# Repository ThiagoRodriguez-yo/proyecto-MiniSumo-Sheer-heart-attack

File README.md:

# proyecto-MiniSumo-Sheer-heart-attack
Este proyecto es de el robot Mini Sumo el cual esta diseñado con la finalidad de ser mostrado en una muestra de fin de año donde se muestre las cosas que podría hacer

--Autores--

 * Vazquez Elias
 * Rodriguez Thiago
 * Uriel Ramirez

 --02/10/2025--

 <---------------------------------------->

-Descripcion tecnica: El Mini Sumo es un robot hecho mas que nada para las competencias de robots, tiene una medida de 10x10 (ancho y largo) y un peso limite de 350 gramos en amateur y 500 gramos en competiciones, usualmente el robot mini sumo no tiene un consumo de energia fijo, ya que depende de sus componentes, sin embargo tomando de ejemplo al robot de Arduino que consume unos 46 mA en reposo y 0,03–0,05 kWh por hora con carga, seria considerado como un consumo mensual bajo de 2–4 kWh.

-Objetivos del proyecto: El objetivo de nuestro proyecto es poder enseñar nuestro robot en la muestra de fin de año y que la gente vea como quedo el resultado final de nuestro proyecto

<----------------------------------------->

--Lista de componentes utilizados--

-Sensores-
Modelo: AD32
Detalles técnicos:
– Voltaje de funcionamiento CC: 3.3 V-5 V.
– Corriente de funcionamiento: 20 mAh
– Temperatura de funcionamiento: -10°C a + 50°C
– Distancia de detección: 2 a 40 cm
– Interfaz IO: 4 líneas (- / + / S / EN)
– Señal de salida: nivel TTL
– Dimensiones: 4.5 x 1.1 cm (aprox.)
– Tipo de sensor: Emisor y receptor infrarrojo (IR)
– Número de pines: 4 pines para conexión.
– Ajuste de sensibilidad: Incluye potenciómetro para calibrar la sensibilidad del sensor.

-Sensores de piso-
Características:
- Usando sensores de reflexión infrarroja TCRT5000
- Distancia de reflexión de prueba: 1mm a 25mm
- Limpio y 3, la salida del comparador, Onda de senal,
- La capacidad de conducción es fuerte, por mas de 15 ma.
- Con muchos potenciómetros de precisión ajustables para ajustar la sensibilidad
- Voltaje de funcionamiento de 3,3 V a 5V
- Forma de salida: salida de interruptor digital (0 y 1)
- Tiene un agujero de perno fijo, instalación conveniente
- Tablero pequeño tamaño de PCB: 3,2 cm x 1,4 cm
- LM393, uso de comparador de amplio voltaje
- Tamaño: 3,1×1,3 cm (aprox.)

-Motores-
Modelo: N30 500RPM
Detalles tecnicos:
- Diámetro de 15 mm y longitud total de 47 mm. 
- Corriente: 120 mA en funcionamiento, 3,2 A en parada.
- Par: 3,9 kg-cm , 1,2 kg-cm .
- Peso: 21 gramos.

-Switch-
Llave Palanca Switch Spdt On-on 6a 125v Mts-102 3pin
Modelo: MTS-102
Detalles tecnicos:
- Tipo: DPDT
- Número de pines: 3 pines
- Posición: 2 Posiciones (ON / ON)
- Tamaño: aprox. 31 * 13 * 12 mm
- Voltaje y corriente nominales: CA 125V, 6A

-Circuito del Motor-
Modelo: DIP8
-Tipo de circuito: Integrado
-Tipo TA6586

-Placa-
Modelo: Nodemcu ESP-325 USB-C 38 pines
Detalles tecnicos:
- Voltaje de Alimentación: 5V (USB-C)
- Voltaje de Entrada / Salida: 3.3V
- Puerto USB: USB-C
- SoC: ESP32
- CPU principal: Tensilica Xtensa 32-bit LX6
- Frecuencia de Reloj: hasta 240Mhz
- Desempeño: Hasta 600 DMIPS
- WiFi: 802.11 b/g/n/e/i
- Bluetooth:v4.2 BR/EDR y Bluetooth Low Energy (BLE)
- Pines Digitales GPIO: 24 
- Convesor Analogolico Digital
- UART: 2
- Chip USB-Serial: CP2102
- Antena en PCB
- 38 PINES
- DIMENSIONES: 51 x 25 mm (Largo y Ancho)

  -Seguridad-
- Estándares IEEE 802.11: WFA, WPA/WPA2 y WAPI
- 1,024-bit OTP
- Aceleración Criptográfica por Hardware: AES, HASH (SHA-2), RSA, ECC, RNG

  -Driver de motores-
Características:
- Baja corriente en espera: ≦2 µA
- Amplio rango de tensión de alimentación
- Función de freno integrada
- Protección contra apagado térmico
- Límite de sobrecorriente y protección contra cortocircuitos
- Encapsulado DIP8 sin plomo.

  -Resistencias-
- Cantidad: 6
- Valores: 3 resistencias de 1k y 3 resistencias de 2.2k

  -Capacitores-
- Tipo de capacitores: Electrolitico y Ceramico
- Cantidad: 2 capacitores Electroliticos y 4 capacitores de Marmol
- Valores Electroliticos: 470uf
- Valores Ceramico: 2 de 0.1uf y 2 de 10nf

  -Diseño del circuito-

ESQ:

PCB:

  -Descripcion del funcionamiento-
- Detección de límites: El robot incorpora un sensor infrarrojo ubicado en la parte inferior del chasis, cuya función principal es identificar el borde de la superficie de combate (arena). Ante la detección de un cambio en el color o textura del suelo que indique el límite, el sistema activa una rutina de evasión para evitar que el robot lo cruce.

- Localización del oponente: El robot está equipado con sensores de proximidad, infrarrojos frontales, que permiten detectar la presencia de un contrincante en su campo de acción. Una vez identificado un objetivo, el robot inicia una secuencia de ataque orientada a la intercepción directa.

- Comportamiento ofensivo: El algoritmo de combate prioriza la ofensiva continua. El robot mantiene su trayectoria de ataque hasta que logra desplazar al oponente fuera de los límites del área de combate, momento en el cual se reinicia el ciclo de búsqueda de nuevos objetivos.

  -Montaje-
lijar la placa de cobre
luego conseguir el sticker del pcb 
acto siguiente planchar el sticker en la placa hasta ver que el tóner haya quedado perfectamente adherido a la placa
luego bañar la placa en percloruro por varios minutos
luego sacar la placa del percloruro después de revisar que no haya excedente de cobre
lijar nuevamente para sacar el tóner excedente
agujerear la placa luego de revisar que el cobre innecesario haya sido comido correctamente por el percloruro
iniciar montaje de componentes electrónicos
luego soldar cada componente a la placa (se recomienda usar el material de soldadura Flux) usar estaño para soldar (usar estaño 60% estaño 40% plomo)
luego verificar que no haya cortos
montaje terminado

  -herramientas-
un soldador de punta fina (de 60W)
estaño (60% estaño 40% plomo)
pinzas(de punta y alicate)
flux
chupa estaño y o cinta desoldante

- precauciones: al manejar herramientas peligrosas en manos inexpertas recomendamos el uso de guantes de seguridad y delantal, aunque estos no son obligatorios

-tipo de soldadura: 
Soldadura con aleación de estaño-plomo  

-Datasheet-

AD32: [E3S-A.PDF](https://github.com/user-attachments/files/23096925/E3S-A.PDF)

ESP32: [ESP32.PDF](https://github.com/user-attachments/files/23096990/ESP32.PDF)

TCRT5000:[TCRT5000.PDF](https://github.com/user-attachments/files/23097029/TCRT5000.PDF)

TA6586:[TA6586.PDF](https://github.com/user-attachments/files/23097099/TA6586.PDF)

-Tareas de cada integrante-
- Rodriguez Thiago: PCB, Esquematico
- Elias Vazquez: Carroceria (3D)
- Uriel Ramirez: Montaje de la placa y programacion

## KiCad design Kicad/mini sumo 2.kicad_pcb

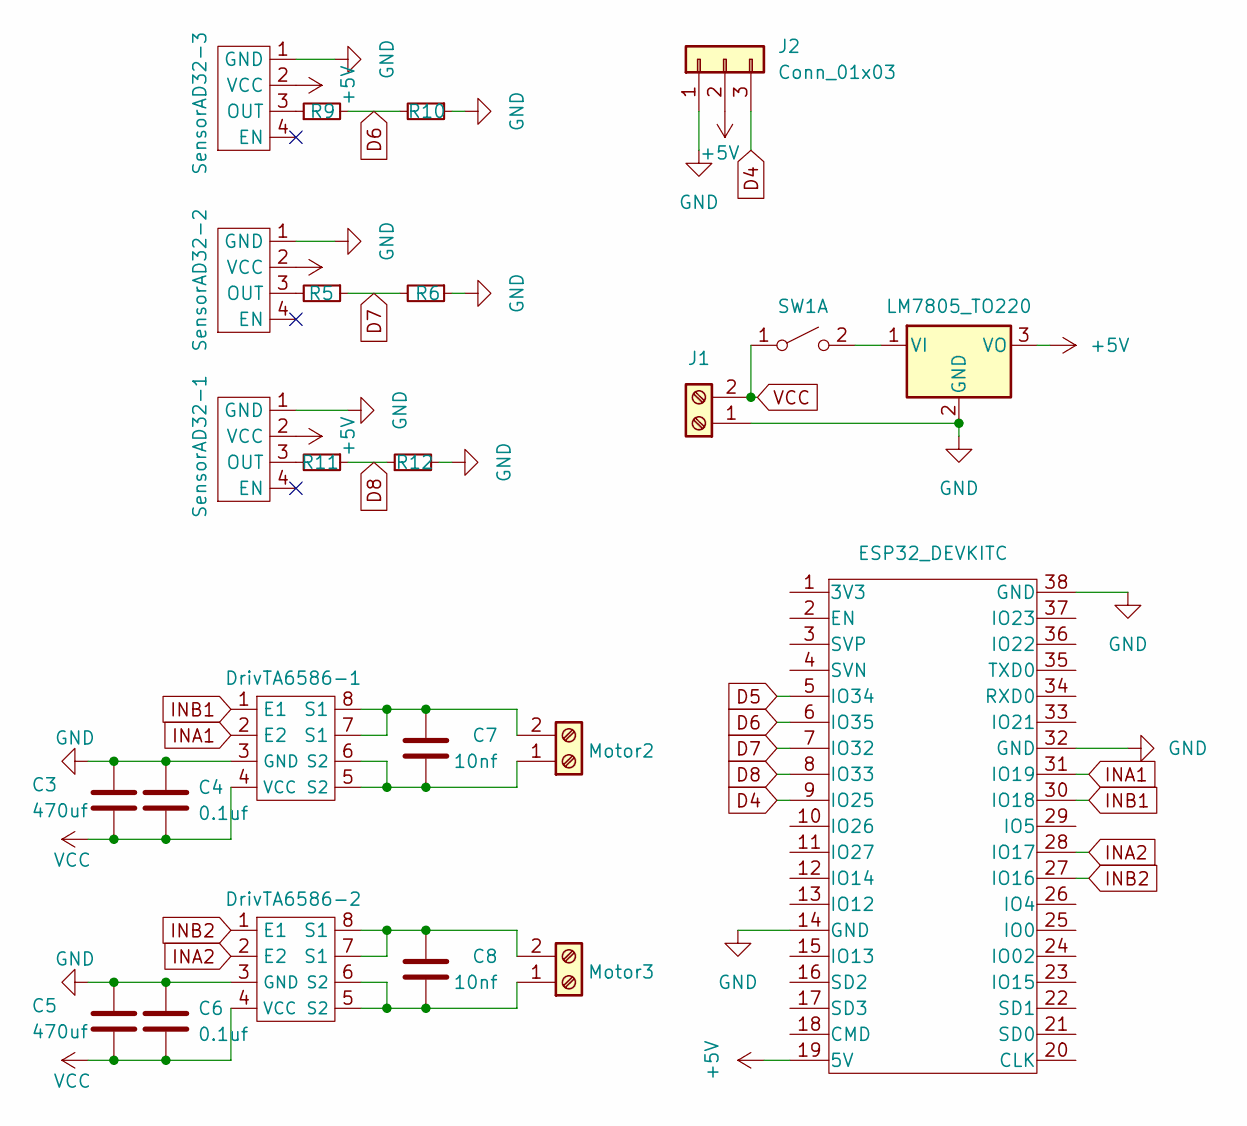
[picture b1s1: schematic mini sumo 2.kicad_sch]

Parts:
C3, C5: 470uf; CP_Radial_D8.0mm_P3.80mm
C4, C6: 0.1uf; C_Disc_D5.0mm_W2.5mm_P2.50mm
C7, C8: 10nf; C_Disc_D5.0mm_W2.5mm_P2.50mm
DrivTA6586-1, DrivTA6586-2: DIP-8_W7.62mm
J1: Screw_Terminal_01x02; TerminalBlock_MaiXu_MX126-5.0-02P_1x02_P5.00mm
J2: Conn_01x03; PinHeader_1x03_P2.54mm_Vertical
Motor2, Motor3: Screw_Terminal_01x02; TerminalBlock_Phoenix_MKDS-1,5-2-5.08_1x02_P5.08mm_Horizont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
R5, R9, R11: 1K; R_Axial_DIN0207_L6.3mm_D2.5mm_P7.62mm_Horizontal
R6, R10, R12: 2.2K; R_Axial_DIN0207_L6.3mm_D2.5mm_P7.62mm_Horizontal
SW1: SW_DPST_x2; SW_SPDT_TH_Vertical
SensorAD32-1, SensorAD32-2, SensorAD32-3: JST-4V
U1: LM7805_TO220; TO-220-3_Vertical
U9: ESP32_DEVKITC; ESP32S

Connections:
+5V: J2.2, SensorAD32-1.2 (VCC), SensorAD32-2.2 (VCC), SensorAD32-3.2 (VCC), U1.3 (VO), U9.19 (5V)
D4: J2.3, U9.9 (IO25)
D5: U9.5 (IO34)
D6: R9.2, R10.2, U9.6 (IO35)
D7: R5.1, R6.2, U9.7 (IO32)
D8: R11.1, R12.1, U9.8 (IO33)
GND: C3.1, C4.1, C5.1, C6.1, DrivTA6586-1.3 (GND), DrivTA6586-2.3 (GND), J1.1, J2.1, R6.1, R10.1, R12.2, SensorAD32-1.1 (GND), SensorAD32-2.1 (GND), SensorAD32-3.1 (GND), U1.2 (GND), U9.14 (GND), U9.32 (GND), U9.38 (GND)
INA1: DrivTA6586-1.2 (E2), U9.31 (IO19)
INA2: DrivTA6586-2.2 (E2), U9.28 (IO17)
INB1: DrivTA6586-1.1 (E1), U9.30 (IO18)
INB2: DrivTA6586-2.1 (E1), U9.27 (IO16)
unnamed: C7.2, DrivTA6586-1.5 (S2), DrivTA6586-1.6 (S2), Motor2.1
unnamed: C7.1, DrivTA6586-1.7 (S1), DrivTA6586-1.8 (S1), Motor2.2
unnamed: C8.2, DrivTA6586-2.5 (S2), DrivTA6586-2.6 (S2), Motor3.1
unnamed: C8.1, DrivTA6586-2.7 (S1), DrivTA6586-2.8 (S1), Motor3.2
unnamed: SW1.2 (B), U1.1 (VI)
unnamed: R11.2, SensorAD32-1.3 (OUT)
unnamed: R5.2, SensorAD32-2.3 (OUT)
unnamed: R9.1, SensorAD32-3.3 (OUT)
VCC: C3.2, C4.2, C5.2, C6.2, DrivTA6586-1.4 (VCC), DrivTA6586-2.4 (VCC), J1.2, SW1.1 (A)

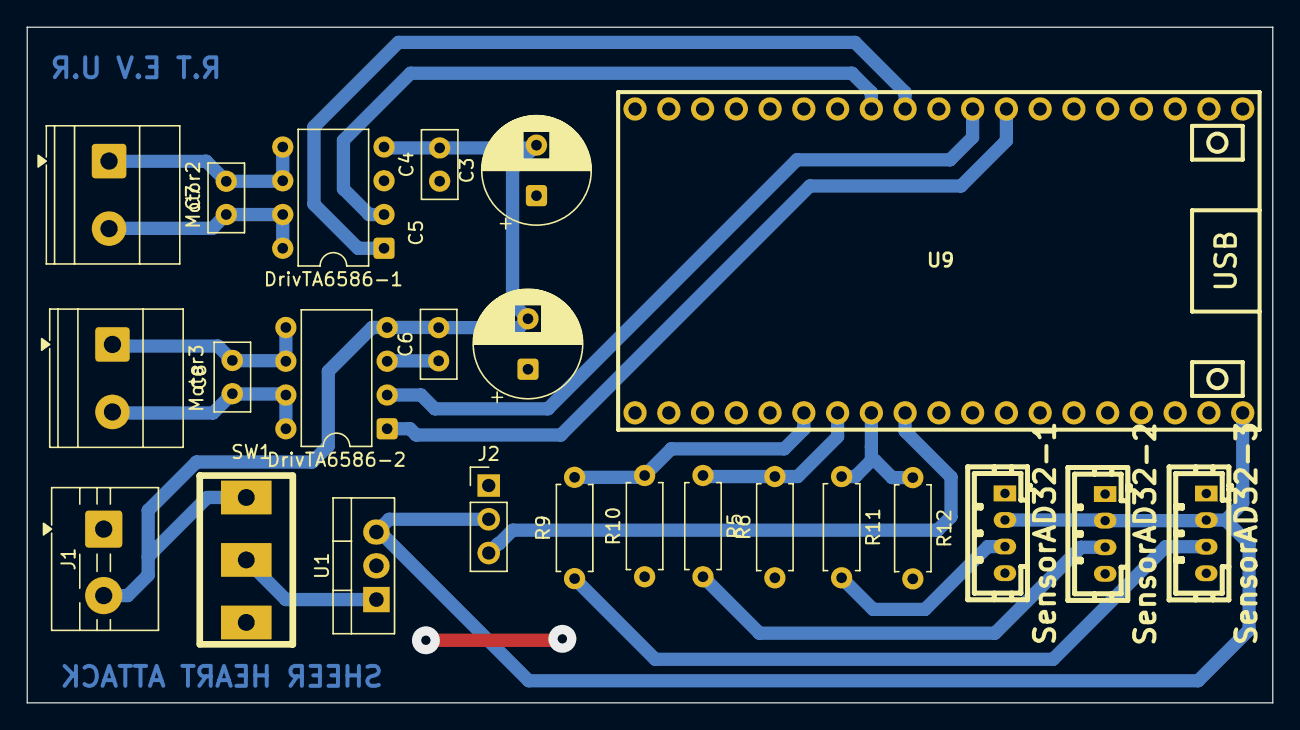
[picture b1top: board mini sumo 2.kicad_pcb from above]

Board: 2 copper layers, 93.7 x 50.8 mm, 24 parts (0 on the bottom side), 19 nets.

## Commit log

2025-10-23 Create codigo
2025-11-27 Rename Captura de pantalla 2025-10-30 084429.png to Esquematico.png
2025-11-27 Rename Captura de pantalla 2025-11-27 102052.png to 3D-Robot.png
2025-11-27 Rename Captura de pantalla 2025-10-30 084342.png to PCB.png
2025-11-27 Rename Captura de pantalla 2025-11-27 101918.png to 3D-PCB.png
2025-11-27 Rename codigo to codigo-ejemplo
